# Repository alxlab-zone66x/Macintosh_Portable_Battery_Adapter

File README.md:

# Macintosh Portable Battery Adapter

This project was created to allow current rectangular 6v lead-acid batteries with spade terminals to be used as a Macintosh Portable battery in a cost effective manner. This is achieved with a spacer made of plastic or cardboard and PCB for the battery contacts. The lead-acid battery is then connected to the PCB via wires with female spade connectors. 

The spacer and PCB is sufficient and the cheapest way to use a 6V lead-acid battery in the portable. This is useful for testing since the battery can be easily swapped. 

There's also a cover that can be 3D printed to give the battery a complete case. Padding should be added to keep the battery from moving around inside the case.

The case is a modified version of the [Macintosh Battery Enclosure 3D model](https://www.thingiverse.com/thing:5185715) done by Stephen Arsenault. Thanks!

### v1.1 Notes

This version moves the solder pad for the wire to provide clearance between the case and the wire.  Slots were added to the PCB for the case cover to slot into. This was done prevent the sides of the case being pushed in easily.

### v1.2 Notes

This version adds supercapacitor support to the PCB. This will allow you to run you're Macintosh Portable with no lead-acid battery! The supercapacitors cover the brief power spikes during hard drive spin up and such that the battery normally handles, so the computer won't shut off when running off the adapter. Supercapacitors are not a substitute for a real lead-acid battery. You won't be able to run without the AC adapter connected. Another difference is that it takes a few minutes for the supercapacitors to charge up before you can use the computer. You can still use a lead-acid battery along with the supercapacitors if you want to.

The supercapacitors need to be balanced since they are used in series. I give two options on the PCB. The best option is to use ALD810025 which is a purpose built supercapacitor balancing IC. The ALD810025 will prolong the life of the supercapacitors and has very low to no leakage. The cheaper alternative is to do passive balancing with resistors. Zener diodes can also be used but I haven't done the calculations to know what the appropriate rating should be. If you're interested in the different types of supercapacitor balancing here's a wonderful [PDF](docs/info/o671684v410%20ANP090a_EN.pdf) by Würth Elecktronik that explains it all. 

It's important to have a recapped Macintosh Portable AC adapter or another 7.5v adapter that actually produces 1.5A. If you haven't recapped your Macintosh Portable adapter and try to use super capacitors only then chances are it will output a lot less than 1.5A and the computer will just shut off when just running on supercapacitors.

### TODO

I would like to modify the v1.2 case so it will protect and separate the supercapacitors from the lead-acid battery if both are installed. 

Upload images of v1.2.

Test on an Macintosh Portable backlight version (M5126).

## 3D Printing Notes

This can be printed without supports. If you're using a FDM printer with a 0.4mm nozzle like I am, then I would recommend printing with at least 3 outer/shell layers to give more strength to the screw holes. 

## Bill of Materials

### v1.0 and v1.1

| Quantity | Product Number                                               |
| :------- | ------------------------------------------------------------ |
| 4        | 6-32 3/8" pan head screws. The same used for 3 1/2" hard drives. (Optional. Only need when using complete battery case) |
| 1        | Red stranded wire, 4 AWG, 20cm for positive terminal         |
| 1        | Black stranded wire, 4 AWG, 20cm for negative terminal       |
| 2        | 4.8mm female spade terminal, crimp type                      |

### v1.2

All the same parts as v1.0 and v1.1 with the addition of the supercapacitor stuff. Use either the IC or the resistors but not both. You can use a supercapacitor with a different capacity, but if you use resistors for balancing, you'll probably need to recalculate the resistance value. Refer to this [PDF](docs/info/o671684v410%20ANP090a_EN.pdf) by Würth Elecktronik to do the calculation.

| Quantity | Description                                               | Designators | Product Number | Datasheet                                |
| :------- | --------------------------------------------------------- | ----------- | -------------- | ---------------------------------------- |
| 1        | Supercapacitor balancing IC.                              | U1          | ALD810025SCL   | [pdf](docs/datasheets/ALD810025.pdf)     |
| 3        | 1/4W 9kOhm resistor (though-hole or 0805)                 | R1,R2,R3    |                |                                          |
| 3        | 10F, 2.7V supercapacitor, 5mm lead spacing, 10mm diameter | C1,C2,C3    | TPL-10/10X30F  | [pdf](docs/datasheets/TPL-10_10X30F.pdf) |

## Manufacturing

The release includes the manufacturing files for JLCPCB specifically. If you need to the gerber files, BOM or component pick & place in a different format then you would have to generate them yourself.

The PCB thickness chosen should be 1.6mm.

## Pictures

## License

Macintosh Portable Battery Adapter by [Alexandre Marcoux](https://github.com/alxlab-zone66x/Macintosh_Portable_Battery_Adapter) licensed under a <a rel="license" href="http://creativecommons.org/licenses/by-nc-sa/4.0/">Creative Commons Attribution-NonCommercial-ShareAlike 4.0 International License</a>.

## Community

For more great retro hardware projects and a great community check out:

Join us in #skunkworks on [Discord](https://discord.gg/GKcvtgU7P9) to help make retro solutions available to all.

## Attribution

Macintosh Portable Battery Enclosure (M5137) by [StephenLulz](https://www.thingiverse.com/StephenLulz) is licensed under the [Creative Commons Attribution 4.0 International License](http://creativecommons.org/licenses/by/4.0/).

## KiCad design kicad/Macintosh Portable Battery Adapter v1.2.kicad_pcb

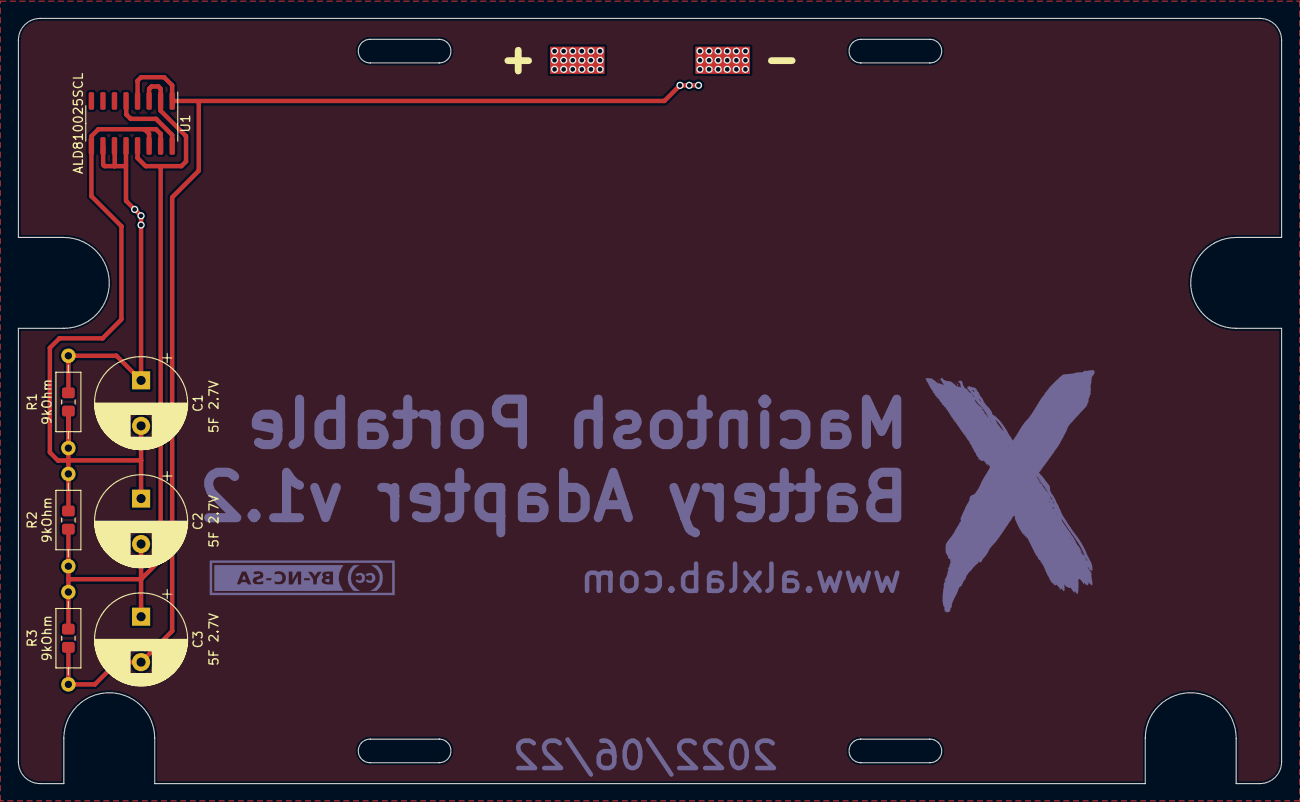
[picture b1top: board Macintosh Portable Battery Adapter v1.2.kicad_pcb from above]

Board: 2 copper layers, 139.0 x 84.2 mm, 16 parts (0 on the bottom side), 4 nets.

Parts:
A1, A2, A3, A4: Macintosh_Portable_Battery_Case_Hole
BT1: Macintosh_Portable_Battery; Macintosh_Portable_Battery_Contacts
C1, C2, C3: 5F 2.7V; CP_Radial_D10.0mm_P5.00mm
J1: Conn_01x02_Female; Macintosh_Portable_Battery_Wire_Pads
R1, R2, R3: 9kOhm; R_Axial_DIN0207_L6.3mm_D2.5mm_P10.16mm_Horizontal
R11, R12, R13: 9kOhm; R_0805_2012Metric_Pad1.20x1.40mm_HandSolder
U1: ALD810025SCL; SOIC-16_3.9x9.9mm_P1.27mm

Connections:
/A1: C2.2, C3.1, R2.2, R3.1, R12.2, R13.1, U1.2 (Dn1), U1.3 (Gn1), U1.13 (Sn2)
/A2: C1.2, C2.1, R1.2, R2.1, R11.2, R12.1, U1.9 (Sn3), U1.14 (Gn2), U1.15 (Dn2)
/V+: BT1.1 (+), C1.1, J1.1, R1.1, R11.1, U1.10 (Gn3), U1.11 (Dn3), U1.12 (V+)
/V-: BT1.2 (-), C3.2, J1.2, R3.2, R13.2, U1.1 (IC), U1.4 (Sn1), U1.5 (V-), U1.16 (IC)

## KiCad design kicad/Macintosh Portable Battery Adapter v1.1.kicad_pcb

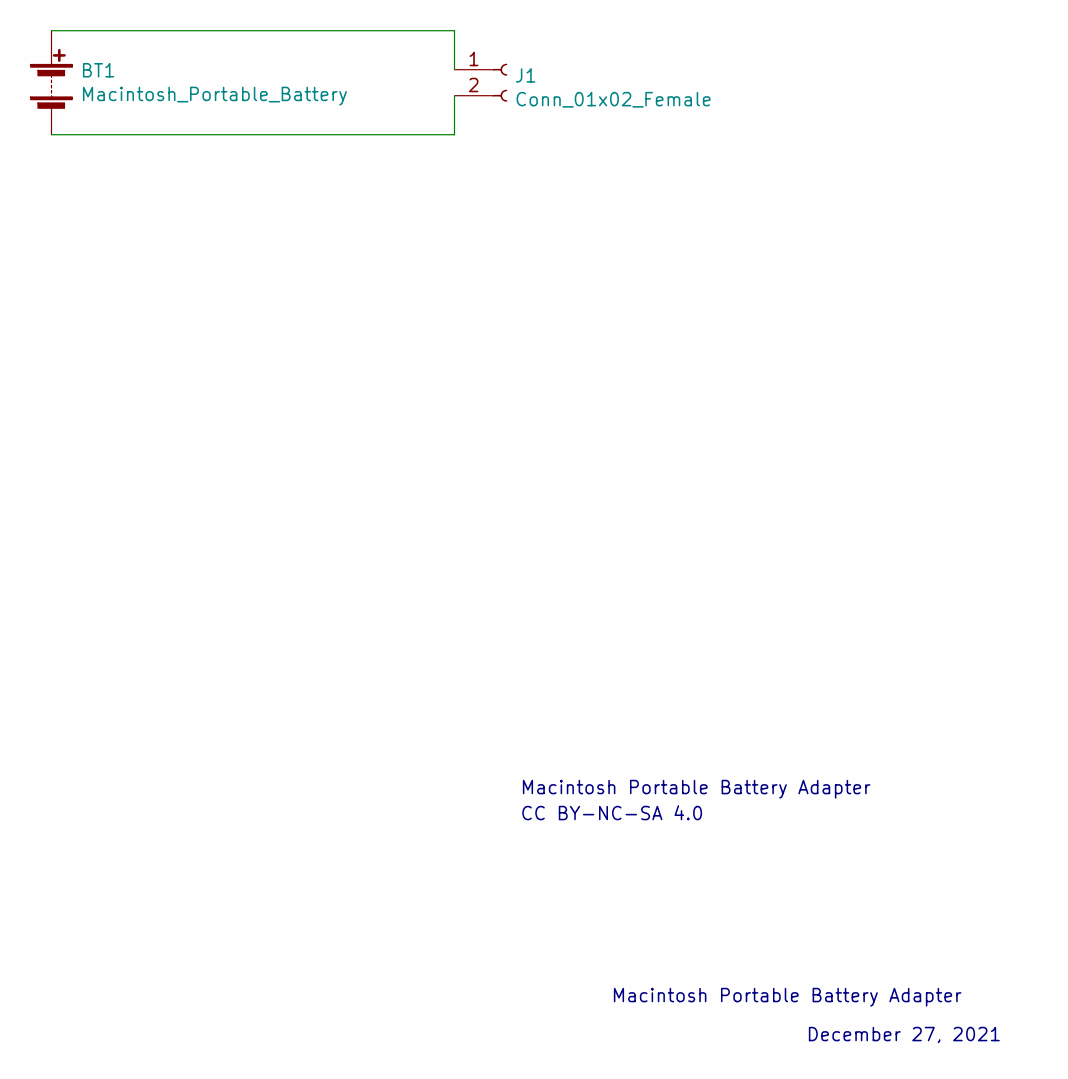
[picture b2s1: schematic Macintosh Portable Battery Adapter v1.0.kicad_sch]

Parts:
BT1: Macintosh_Portable_Battery; Macintosh_Portable_Battery_Contacts
J1: Conn_01x02_Female; Macintosh_Portable_Battery_Wire_Pads

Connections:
unnamed: BT1.1 (+), J1.1
unnamed: BT1.2 (-), J1.2

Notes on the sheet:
CC BY-NC-SA 4.0
Macintosh Portable Battery Adapter
December 27, 2021

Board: 2 copper layers, 6 parts (0 on the bottom side), 2 nets, no tracks yet.

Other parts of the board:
A1, A2, A3, A4: Macintosh_Portable_Battery_Case_Hole

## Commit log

2022-04-15 Macintosh Portable Battery Adapter v1.0
2022-04-15 Add attribution for case.
2022-06-29 Version 1.1
2022-06-29 Add version 1.2 kicad and gerber files
2023-03-19 Update README for v1.2
    Add missing 3D case model for v1.2
